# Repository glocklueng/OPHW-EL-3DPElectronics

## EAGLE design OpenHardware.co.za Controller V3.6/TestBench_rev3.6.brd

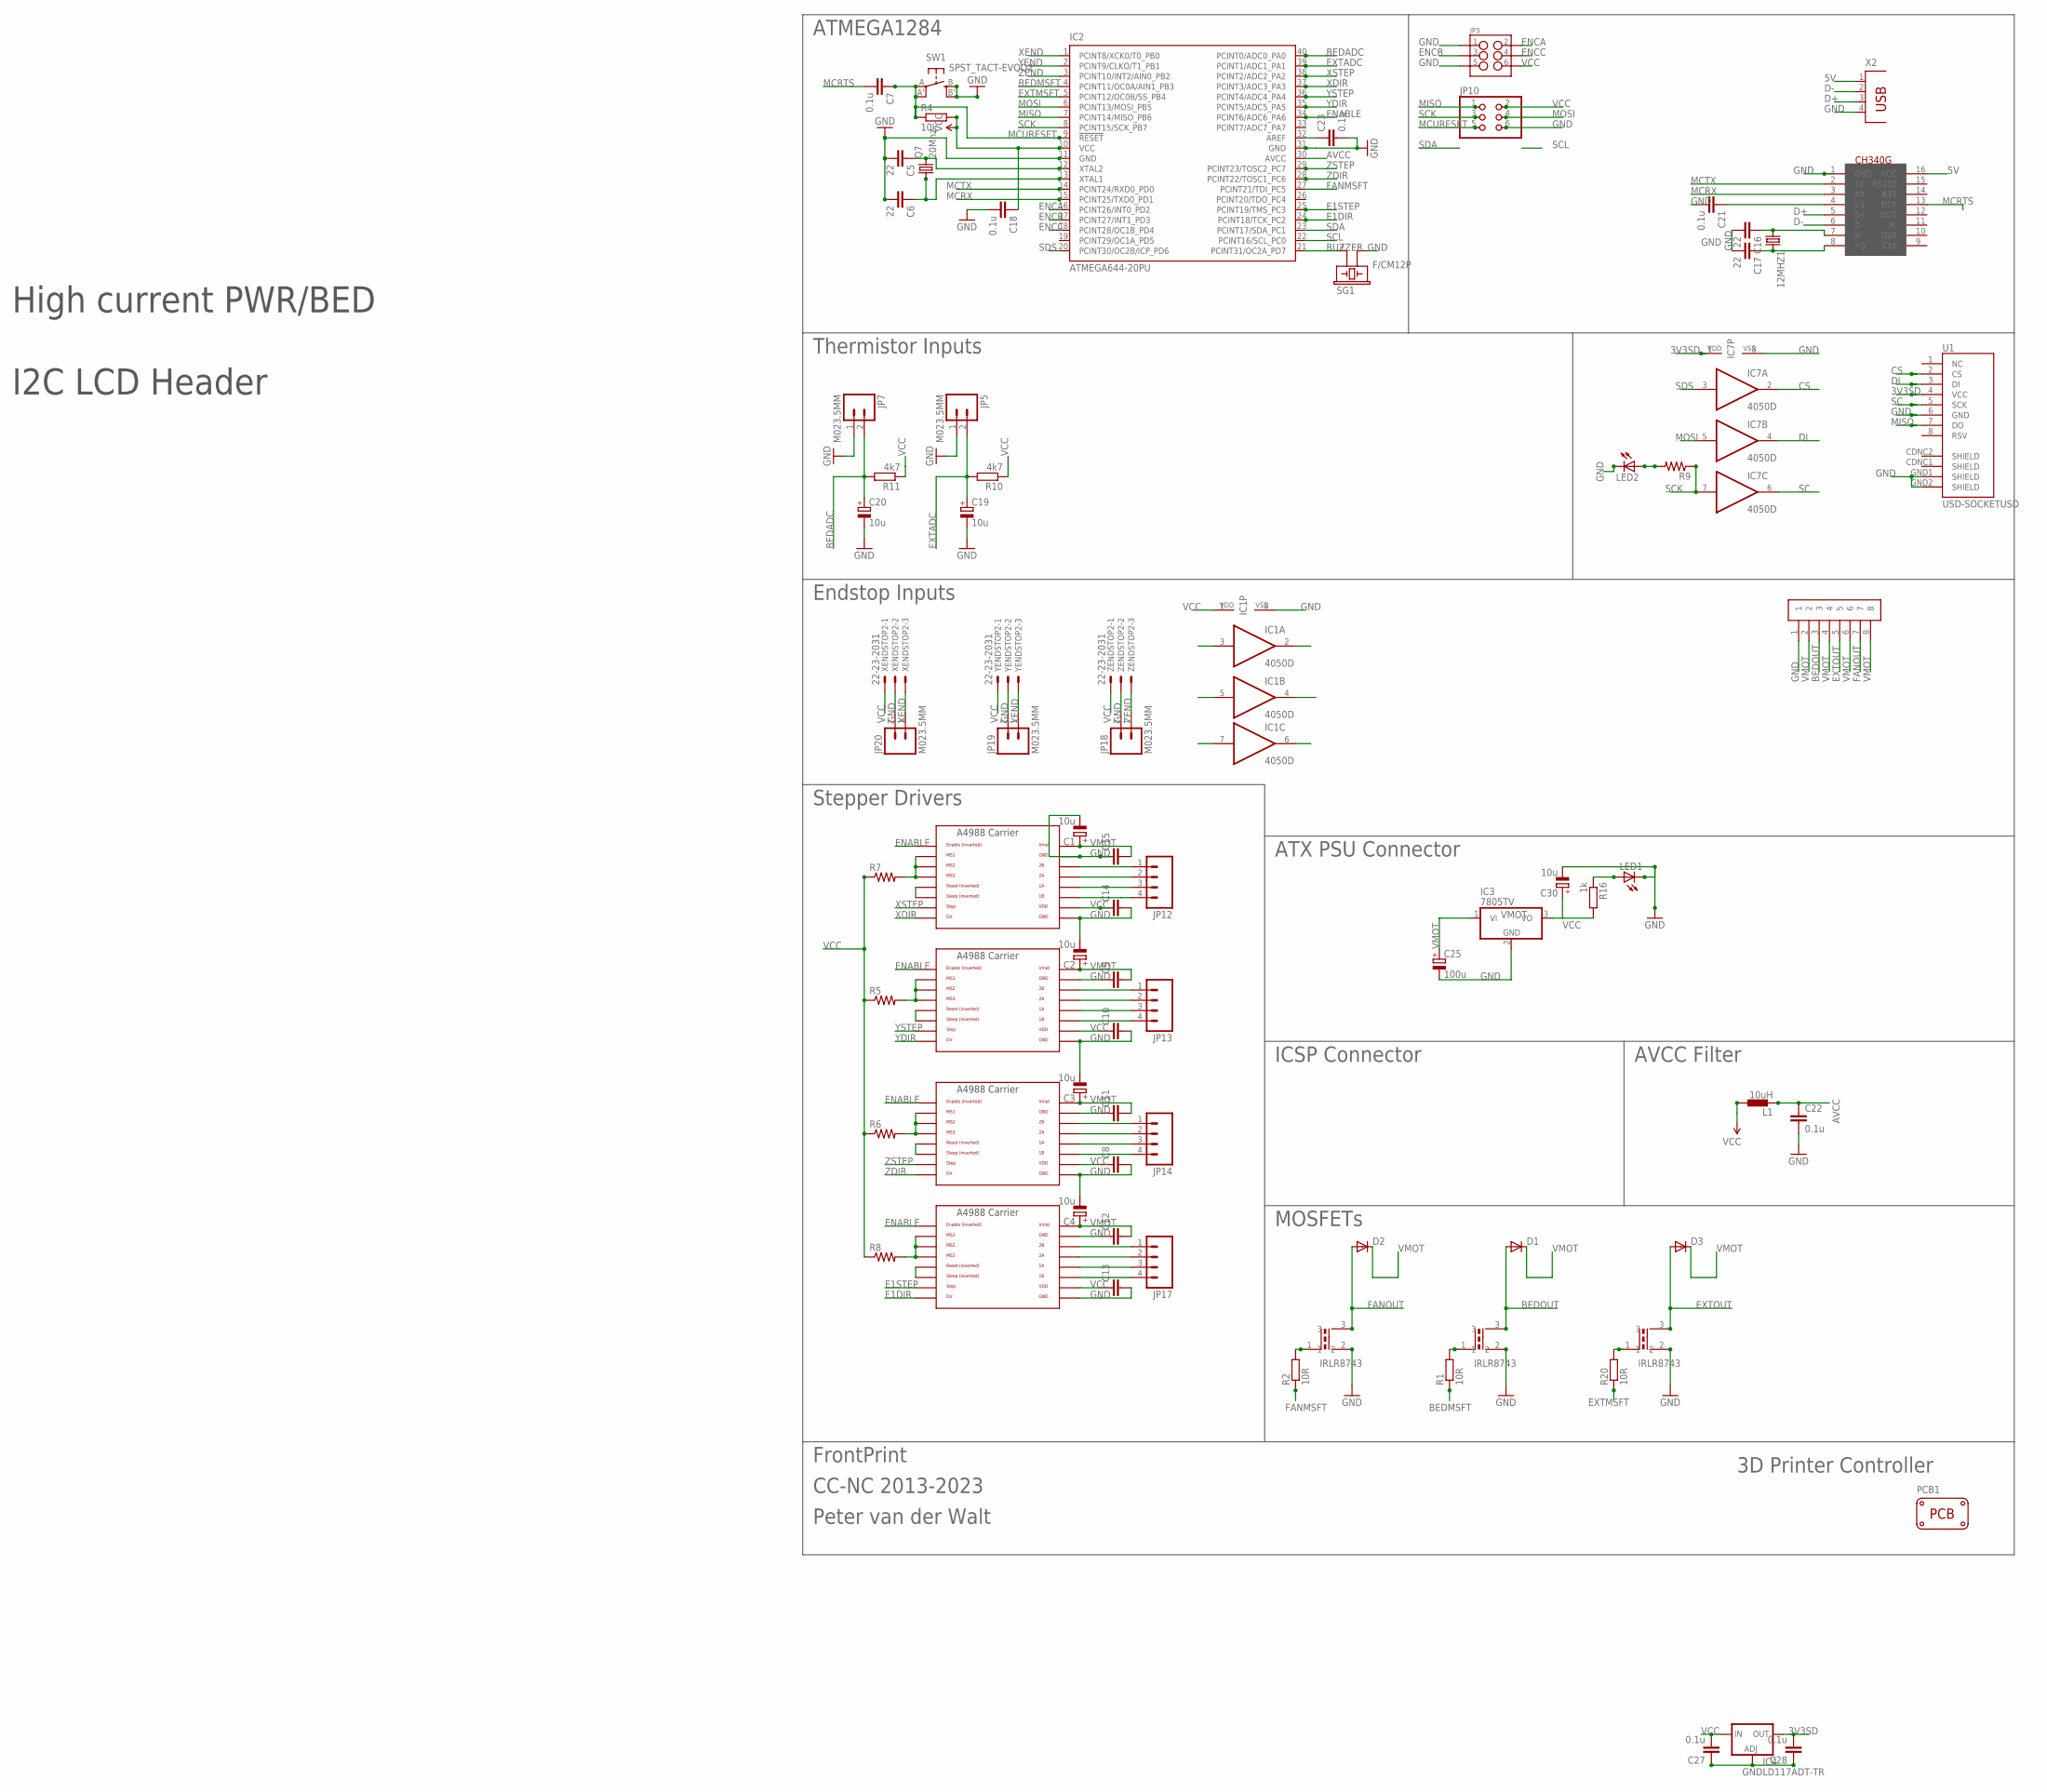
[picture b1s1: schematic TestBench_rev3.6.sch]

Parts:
12MHZ1: CRYSTALHC49UP; HC49UP
C1, C2, C3, C4, C19, C20, C30: 10u; SANYO-OSCON_SMD_B6
C5, C6, C16, C17: 22; 1206
C7, C18, C21, C22, C23, C27, C28: 0.1u; 1206
C8, C9, C10, C11, C12, C13, C14, C15: CAP1206; 1206
C25: 100u; E5-8,5
D1, D2, D3: DIODESMA-ALT; SMA-DIODE_ALT
E1POL: POLOLU_A4983CARRIER; A4988BREAKOUT
IC1, IC7: 4050D; SO16
IC2: ATMEGA644-20PU; DIL40
IC3: 7805TV; TO220V
IC4: LD117ADT-TR; DPACK
JP3: M03X2SHROUD; 2X3-SHROUDED
JP5, JP7, JP18, JP19, JP20: M023.5MM; SCREWTERMINAL-3.5MM-2
JP10: PINHD-2X3/90; 2X03/90
JP12, JP13, JP14, JP17: M04SCREW; SCREWTERMINAL-3.5MM-4
L1: 10uH; BL01RN1A
LED1, LED2: LEDSMT1206; 1206
PCB1: PCB_DP_SQUARE-10X10; DP100100_V1
Q7: 20Mhz; HC49UP
R1, R2, R20: 10R; M1206
R4: 10k; M1206
R5, R6, R7, R8: RESISTOR1206; 1206
R9: R-US_M1206; M1206
R10, R11: 4k7; M1206
R16: 1k; M1206
SG1: F/CM12P
SW1: SPST_TACT-EVQQ2; EVQ-Q2
U1: USD-SOCKETUSD; USD-SOCKET-PP
U$1, U$3, U$4: IRLR8743; TO263
U$2: CH340G; SOIC16
U$5: XY825A-8P
X2: PN61729
XENDSTOP2: 22-23-2031
XPOL: POLOLU_A4983CARRIER; A4988BREAKOUT
YENDSTOP2: 22-23-2031
YPOL: POLOLU_A4983CARRIER; A4988BREAKOUT
ZENDSTOP2: 22-23-2031
ZPOL: POLOLU_A4983CARRIER; A4988BREAKOUT

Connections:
3V3SD: C28.2, IC4.4 (OUT), IC7.1 (VDD), U1.4 (VCC)
5V: U$2.16 (VCC), X2.1
AVCC: C22.1, IC2.30 (AVCC), L1.1
BEDADC: C20.+, IC2.40 (PCINT0/ADC0_PA0), JP7.2, R11.2
BEDMSFT: IC2.4 (PCINT11/OC0A/AIN1_PB3), R1.1
BEDOUT: D1.A, U$3.3, U$5.3
BUZZER: IC2.21 (PCINT31/OC2A_PD7), SG1.+ (1)
CS: IC7.2 (O), U1.2 (CS)
D+: U$2.5 (D+), X2.3
D-: U$2.6 (D-), X2.2
DI: IC7.4 (O), U1.3 (DI)
E1DIR: E1POL.DIR, IC2.24 (PCINT18/TCK_PC2)
E1STEP: E1POL.STEP, IC2.25 (PCINT19/TMS_PC3)
ENABLE: E1POL.EN, IC2.34 (PCINT6/ADC6_PA6), XPOL.EN, YPOL.EN, ZPOL.EN
ENCA: IC2.16 (PCINT26/INT0_PD2), JP3.2
ENCB: IC2.17 (PCINT27/INT1_PD3), JP3.3
ENCC: IC2.18 (PCINT28/OC1B_PD4), JP3.4
EXTADC: C19.+, IC2.39 (PCINT1/ADC1_PA1), JP5.2, R10.2
EXTMSFT: IC2.5 (PCINT12/OC0B/SS_PB4), R20.1
EXTOUT: D3.A, U$1.3, U$5.5
FANMSFT: IC2.27 (PCINT21/TDI_PC5), R2.1
FANOUT: D2.A, U$4.3, U$5.7
GND: C1.-, C2.-, C3.-, C4.-, C5.2, C6.2, C8.2, C9.1, C10.2, C11.1, C12.1, C13.2, C14.2, C15.1, C16.2, C17.2, C18.2, C19.-, C20.-, C21.2, C22.2, C23.2, C25.-, C27.1, C28.1, C30.-, E1POL.GND, E1POL.GND@0 (GND), IC1.8 (VSS), IC2.11 (GND), IC2.31 (GND), IC3.2 (GND), IC4.1 (ADJ), IC7.8 (VSS), JP3.1, JP3.5, JP5.1, JP7.1, JP10.6, JP18.2, JP19.2, JP20.2, LED1.C, LED2.C, SG1.- (2), SW1.B (S), SW1.B' (S1), U1.6 (GND), U1.GND1 (SHIELD), U1.GND2 (SHIELD), U$1.2 (1), U$2.1 (GND), U$3.2 (1), U$4.2 (1), U$5.1, X2.4, XENDSTOP2.2, XPOL.GND, XPOL.GND@0 (GND), YENDSTOP2.2, YPOL.GND, YPOL.GND@0 (GND), ZENDSTOP2.2, ZPOL.GND, ZPOL.GND@0 (GND)
MCRTS: C7.2, U$2.13 (DTR)
MCRX: IC2.15 (PCINT25/TXD0_PD1), U$2.3 (RX)
MCTX: IC2.14 (PCINT24/RXD0_PD0), U$2.2 (TX)
MCURESET: C7.1, IC2.9 (!RESET), JP10.5, R4.1, SW1.A, SW1.A' (P1)
MISO: IC2.7 (PCINT14/MISO_PB6), JP10.1, U1.7 (DO)
MOSI: IC2.6 (PCINT13/MOSI_PB5), IC7.5 (I), JP10.4
unnamed: R1.2, U$3.1 (2)
unnamed: R2.2, U$4.1 (2)
unnamed: C5.1, IC2.12 (XTAL2), Q7.2
unnamed: C6.1, IC2.13 (XTAL1), Q7.1
unnamed: E1POL.RST, E1POL.SLP (SLEEP)
unnamed: ZPOL.RST, ZPOL.SLP (SLEEP)
unnamed: YPOL.RST, YPOL.SLP (SLEEP)
unnamed: XPOL.RST, XPOL.SLP (SLEEP)
unnamed: R7.2, XPOL.MS1, XPOL.MS2, XPOL.MS3
unnamed: R5.2, YPOL.MS1, YPOL.MS2, YPOL.MS3
unnamed: E1POL.MS1, E1POL.MS2, E1POL.MS3, R8.2
unnamed: R6.2, ZPOL.MS1, ZPOL.MS2, ZPOL.MS3
unnamed: E1POL.1B, JP17.4
unnamed: E1POL.1A, JP17.3
unnamed: E1POL.2A, JP17.2
unnamed: E1POL.2B, JP17.1
unnamed: JP14.4, ZPOL.1B
unnamed: JP14.3, ZPOL.1A
unnamed: JP14.2, ZPOL.2A
unnamed: JP14.1, ZPOL.2B
unnamed: JP13.1, YPOL.2B
unnamed: JP13.2, YPOL.2A
unnamed: JP13.3, YPOL.1A
unnamed: JP13.4, YPOL.1B
unnamed: JP12.4, XPOL.1B
unnamed: JP12.3, XPOL.1A
unnamed: JP12.2, XPOL.2A
unnamed: JP12.1, XPOL.2B
unnamed: 12MHZ1.1, C16.1, U$2.7 (XI)
unnamed: LED2.A, R9.2
unnamed: 12MHZ1.2, C17.1, U$2.8 (XO)
unnamed: C21.1, U$2.4 (V3)
unnamed: R20.2, U$1.1 (2)
unnamed: C23.1, IC2.32 (AREF)
unnamed: LED1.A, R16.1
SC: IC7.6 (O), U1.5 (SCK)
SCK: IC2.8 (PCINT15/SCK_PB7), IC7.7 (I), JP10.3, R9.1
SCL: IC2.22 (PCINT16/SCL_PC0)
SDA: IC2.23 (PCINT17/SDA_PC1)
SDS: IC2.20 (PCINT30/OC2B/ICP_PD6), IC7.3 (I)
VCC: C8.1, C10.1, C13.1, C14.1, C18.1, C27.2, C30.+, E1POL.VDD, IC1.1 (VDD), IC2.10 (VCC), IC3.3 (VO), IC4.3 (IN), JP3.6, JP10.2, L1.2, R4.2, R5.1, R6.1, R7.1, R8.1, R10.1, R11.1, R16.2, XENDSTOP2.1, XPOL.VDD, YENDSTOP2.1, YPOL.VDD, ZENDSTOP2.1, ZPOL.VDD
VMOT: C1.+, C2.+, C3.+, C4.+, C9.2, C11.2, C12.2, C15.2, C25.+, D1.C, D2.C, D3.C, E1POL.VMOT, IC3.1 (VI), U$5.2, U$5.4, U$5.6, U$5.8, XPOL.VMOT, YPOL.VMOT, ZPOL.VMOT
XDIR: IC2.37 (PCINT3/ADC3_PA3), XPOL.DIR
XEND: IC2.1 (PCINT8/XCK0/T0_PB0), JP20.1, XENDSTOP2.3
XSTEP: IC2.38 (PCINT2/ADC2_PA2), XPOL.STEP
YDIR: IC2.35 (PCINT5/ADC5_PA5), YPOL.DIR
YEND: IC2.2 (PCINT9/CLKO/T1_PB1), JP19.1, YENDSTOP2.3
YSTEP: IC2.36 (PCINT4/ADC4_PA4), YPOL.STEP
ZDIR: IC2.28 (PCINT22/TOSC1_PC6), ZPOL.DIR
ZEND: IC2.3 (PCINT10/INT2/AIN0_PB2), JP18.1, ZENDSTOP2.3
ZSTEP: IC2.29 (PCINT23/TOSC2_PC7), ZPOL.STEP

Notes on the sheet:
Thermistor Inputs
Endstop Inputs
Stepper Drivers
AVCC Filter
ATX PSU Connector
ICSP Connector
MOSFETs
ATMEGA1284
FrontPrint
CC-NC 2013-2023
Peter van der Walt
3D Printer Controller
High current PWR/BED
I2C LCD Header

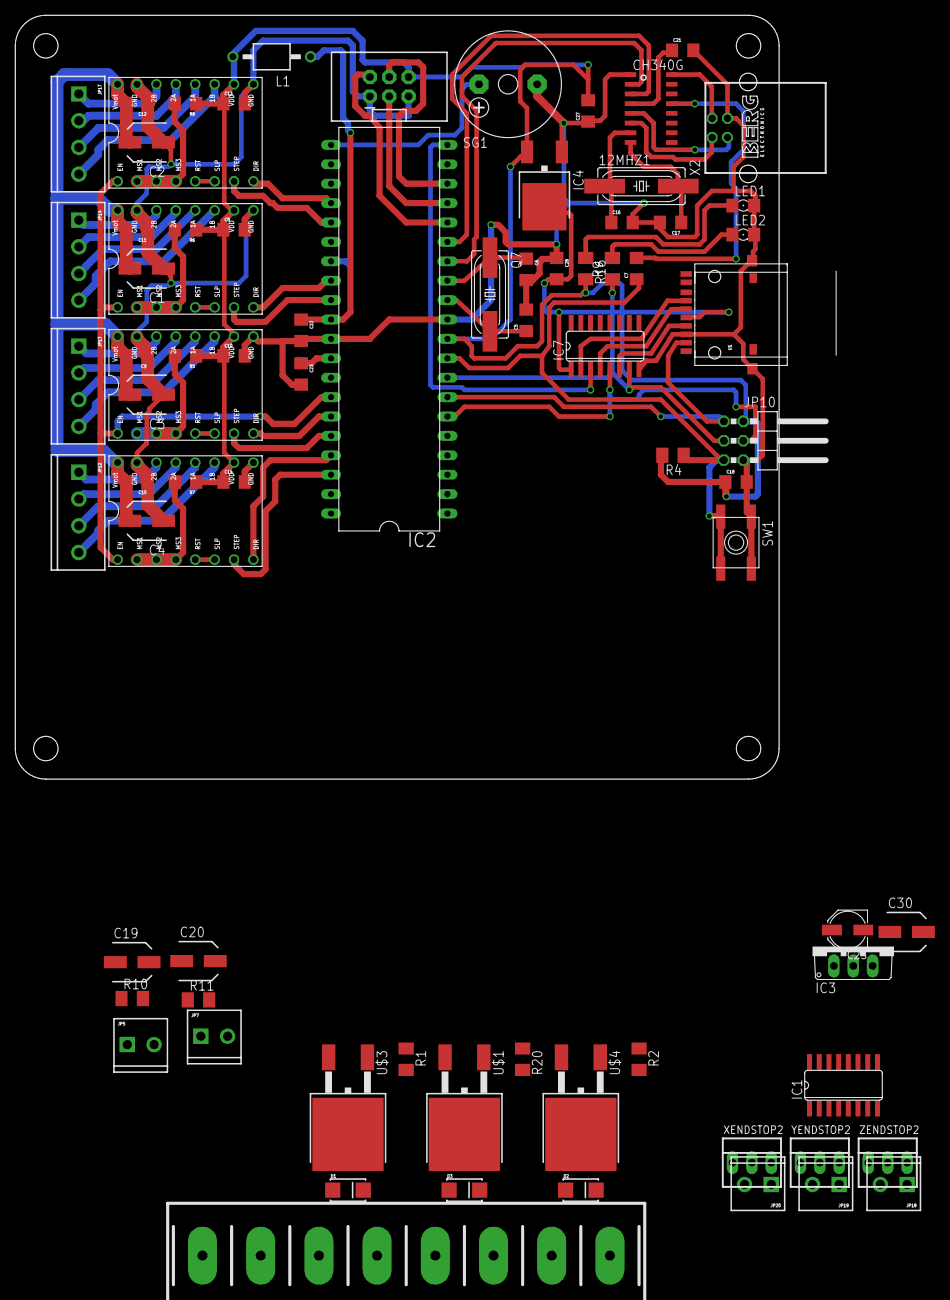
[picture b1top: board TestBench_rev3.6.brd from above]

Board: 2 copper layers, 100.0 x 100.0 mm, 80 parts (0 on the bottom side), 78 nets.

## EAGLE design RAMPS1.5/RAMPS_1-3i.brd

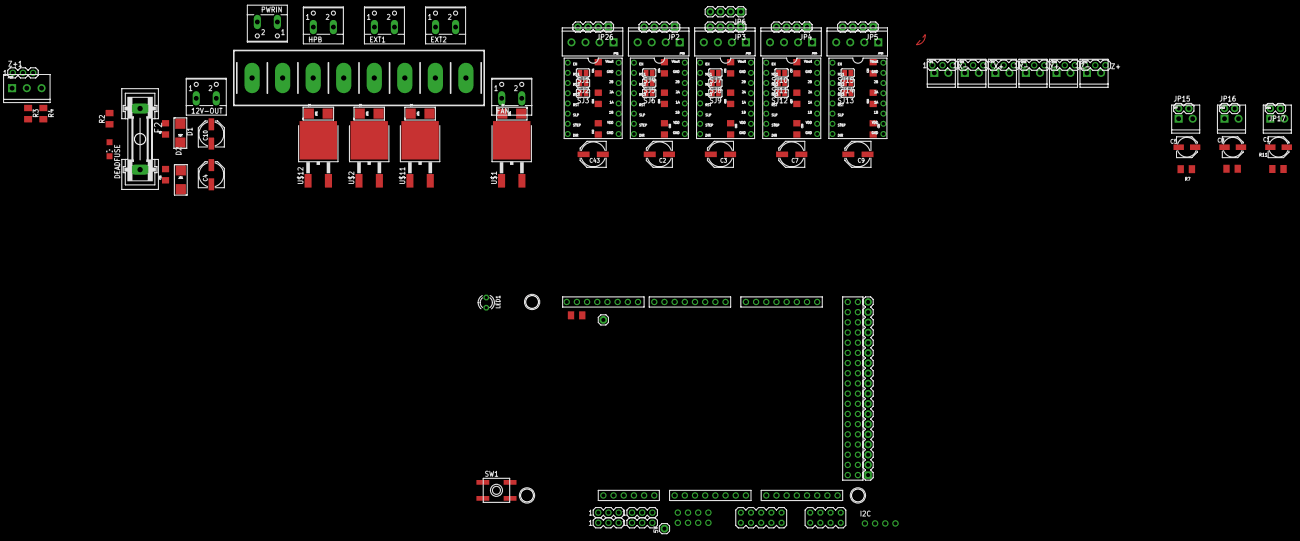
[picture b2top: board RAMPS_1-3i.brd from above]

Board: 2 copper layers, 119 parts (0 on the bottom side), 129 nets, no tracks yet.

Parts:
5V: 1X01
12V-OUT: W237-102
A-OUT: 1X04
C1, C5, C8: 10uF; PANASONIC_C
C2, C3, C7, C9, C43: 100U; PANASONIC_D
C4, C10: 470U; PANASONIC_D
C6, C11: 100n; 1206
C33, C34, C35, C36, C37, C38, C39, C40, C41, C42: 1206
D1, D2, D3, D4, D5, D6: SMADIODE
DEADFUSE: CHIPLED_1206
E1POL1, E2POL1: POLOLU_A4983CARRIER; A4988BREAKOUT
EXT1, EXT2: W237-102
F2: FUSEGSH15; GSH15
FAN: W237-102
HPB: W237-102
I2C: 1X04
JP1, JP7, JP8, JP9, JP10, JP11, JP12, JP13, JP14: M023.5MM; SCREWTERMINAL-3.5MM-2
JP2, JP3, JP4, JP5, JP6, JP26: 1X04
JP15, JP16, JP17: M02PTH; 1X02
JP18: SCREWTERMINAL-3.5MM-3_LOCK.007S
JP21, JP22, JP23, JP24, JP25: SCREWTERMINAL-3.5MM-4
LED1: LED3MM
PS-ON: 1X01
PWRIN: W237-102
R1, R7, R11: 4.7K; M1206
R2, R12: 1K; M1206
R3: 15K; M1206
R4: 10K; M1206
R24, R25, R26, R27, R28: 1206
SER1, SER2, SER3, SER4: 3PIN-HEADER
SERIAL: 1X04
SJ1, SJ2, SJ3, SJ4, SJ5, SJ6, SJ7, SJ8, SJ9, SJ10, SJ11, SJ12, SJ13, SJ14, SJ15: SJ
SW1: SPST_TACT-EVQQ2; EVQ-Q2
U1: ARDUINO_MEGA_SHIELD
U$1, U$2, U$11, U$12: IRLR8743; TO263
U$3: M04X2; 2X4
U$4: XY825A-8P
U$9: M18_; 1X18
U$10: M05X2; 2X5
X+: 3PIN-HEADER
X-: 3PIN-HEADER
XPOL1: POLOLU_A4983CARRIER; A4988BREAKOUT
Y+: 3PIN-HEADER
Y-: 3PIN-HEADER
YPOL1: POLOLU_A4983CARRIER; A4988BREAKOUT
Z+, Z+1: 3PIN-HEADER
Z-: 3PIN-HEADER
ZPOL1: POLOLU_A4983CARRIER; A4988BREAKOUT

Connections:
12V: JP18.1, Z+1.1
+12V: 12V-OUT.1, C6.2, C10.+, D1.A, D6.C, FAN.2
+24V: C4.+, C11.2, D2.C, D3.C, D4.C, D5.C, DEADFUSE.C, EXT1.2, EXT2.2, F2.2, HPB.2, U$4.6, U$4.8
A3: SERIAL.3, U1.A3
A4: SERIAL.4, U1.A4
A5: U1.A5, U$10.3
A9: U1.A9, U$10.4
A10: U1.A10, U$10.5
A11: U1.A11, U$10.10
A12: U1.A12, U$10.9
AM-VIN: D1.C, U1.VIN
BEDOUT: D3.A, HPB.1, U$2.3, U$4.3
D1: A-OUT.4, U1.RX
D2: A-OUT.3, U1.TX
D4: SER4.3, U1.D4
D5: SER3.3, U1.D5
D6: SER2.3, U1.D6
D7: SER1.3, U1.D7
D8-HPB: U1.D8, U$2.1
D9-E2: U1.D9, U$11.1
D10-E1: U1.D10, U$12.1
D12: PS-ON.1, U1.D12
D16: U1.D16, U$9.18
D17: U1.D17, U$9.17
D23: U1.D23, U$9.16
D25: U1.D25, U$9.15
D27: U1.D27, U$9.14
D29: U1.D29, U$9.13
D31: U1.D31, U$9.12
D32: U1.D32, U$9.3
D33: U1.D33, U$9.11
D35: U1.D35, U$9.10
D37: U1.D37, U$9.9
D39: U1.D39, U$9.8
D40: U1.D40, U$10.6
D41: U1.D41, U$9.7
D42: U1.D42, U$10.8
D43: U1.D43, U$9.6
D44: U1.D44, U$10.7
D45: U1.D45, U$9.5
D47: U1.D47, U$9.4
D49: U1.D49, U$3.2
D53: U1.D53, U$3.6
E0-DIR: E1POL1.DIR, U1.D28
E0-EN: E1POL1.EN, U1.D24
E0-STEP: E1POL1.STEP, U1.D26
E1-DIR: E2POL1.DIR, U1.D34
E1-EN: E2POL1.EN, U1.D30
E1-STEP: E2POL1.STEP, U1.D36
E1OUT: D4.A, EXT1.1, U$4.5, U$12.3
E2OUT: D5.A, EXT2.1, U$4.7, U$11.3
FANOUT: D6.A, FAN.1, U$1.3
GND: 12V-OUT.2, A-OUT.2, C1.-, C2.-, C3.-, C4.-, C5.-, C6.1, C7.-, C8.-, C9.-, C10.-, C11.1, C33.2, C34.1, C35.2, C36.1, C37.1, C38.2, C39.2, C40.1, C41.1, C42.2, C43.-, D2.A, E1POL1.GND, E1POL1.GND@0, E2POL1.GND, E2POL1.GND@0, I2C.2, JP1.2, JP7.1, JP8.2, JP9.2, JP10.2, JP11.2, JP12.2, JP13.1, JP14.1, JP15.1, JP16.1, JP17.1, JP18.3, LED1.K, PWRIN.2, R4.1, SER1.1, SER2.1, SER3.1, SER4.1, SERIAL.2, SW1.A, SW1.A', U1.GND@0, U1.GND@1, U1.GND@3, U1.GND@4, U$1.2, U$2.2, U$3.7, U$4.1, U$9.2, U$10.2, U$11.2, U$12.2, X+.2, X-.2, XPOL1.GND, XPOL1.GND@0, Y+.2, Y-.2, YPOL1.GND, YPOL1.GND@0, Z+.2, Z+1.3, Z-.2, ZPOL1.GND, ZPOL1.GND@0
LED: R12.2, U1.D13
MISO: U1.D50, U$3.3
MOSI: U1.D51, U$3.4
unnamed: DEADFUSE.A, R2.1
unnamed: SJ2.2, XPOL1.MS2
unnamed: SJ1.2, XPOL1.MS1
unnamed: SJ4.2, YPOL1.MS1
unnamed: SJ5.2, YPOL1.MS2
unnamed: SJ7.2, ZPOL1.MS1
unnamed: SJ8.2, ZPOL1.MS2
unnamed: SJ9.2, ZPOL1.MS3
unnamed: SJ6.2, YPOL1.MS3
unnamed: SJ3.2, XPOL1.MS3
unnamed: E2POL1.MS2, SJ14.2
unnamed: E2POL1.MS3, SJ13.2
unnamed: E2POL1.MS1, SJ15.2
unnamed: E1POL1.MS3, SJ12.2
unnamed: E1POL1.MS1, SJ10.2
unnamed: E1POL1.MS2, SJ11.2
unnamed: LED1.A, R12.1
unnamed: E1POL1.RST, E1POL1.SLP
unnamed: ZPOL1.RST, ZPOL1.SLP
unnamed: YPOL1.RST, YPOL1.SLP
unnamed: XPOL1.RST, XPOL1.SLP
unnamed: R26.2, SJ1.1, SJ2.1, SJ3.1
unnamed: R24.2, SJ4.1, SJ5.1, SJ6.1
unnamed: R27.2, SJ10.1, SJ11.1, SJ12.1
unnamed: R25.2, SJ7.1, SJ8.1, SJ9.1
unnamed: E1POL1.1B, JP4.4, JP24.4
unnamed: E1POL1.1A, JP4.3, JP24.3
unnamed: E1POL1.2A, JP4.2, JP24.2
unnamed: E1POL1.2B, JP4.1, JP24.1
unnamed: JP3.4, JP6.4, JP23.4, ZPOL1.1B
unnamed: JP3.3, JP6.3, JP23.3, ZPOL1.1A
unnamed: JP3.2, JP6.2, JP23.2, ZPOL1.2A
unnamed: JP3.1, JP6.1, JP23.1, ZPOL1.2B
unnamed: JP2.1, JP22.1, YPOL1.2B
unnamed: JP2.2, JP22.2, YPOL1.2A
unnamed: JP2.3, JP22.3, YPOL1.1A
unnamed: JP2.4, JP22.4, YPOL1.1B
unnamed: JP21.4, JP26.4, XPOL1.1B
unnamed: JP21.3, JP26.3, XPOL1.1A
unnamed: JP21.2, JP26.2, XPOL1.2A
unnamed: JP21.1, JP26.1, XPOL1.2B
unnamed: E2POL1.RST, E2POL1.SLP
unnamed: R28.2, SJ13.1, SJ14.1, SJ15.1
unnamed: E2POL1.1B, JP5.4, JP25.4
unnamed: E2POL1.1A, JP5.3, JP25.3
unnamed: E2POL1.2A, JP5.2, JP25.2
unnamed: E2POL1.2B, JP5.1, JP25.1
PWRIN: F2.1, PWRIN.1, R2.2, U$4.2
RESET: SW1.B, SW1.B', U1.RES
SCK: U1.D52, U$3.5
SCL: I2C.4, U1.D21
SDA: I2C.3, U1.D20
SENSOROUT: JP18.2, R3.1, Z+1.2
THERM0: C5.+, JP7.2, JP15.2, R7.1, U1.A13
THERM1: C8.+, JP13.2, JP16.2, R1.1, U1.A14
THERM2: C1.+, JP14.2, JP17.2, R11.1, U1.A15
VCC: 5V.1, A-OUT.1, C33.1, C35.1, C38.1, C39.1, C42.1, E1POL1.VDD, E2POL1.VDD, I2C.1, R1.2, R7.2, R11.2, R24.1, R25.1, R26.1, R27.1, R28.1, SER1.2, SER2.2, SER3.2, SER4.2, SERIAL.1, U1.5V@0, U1.5V@1, U1.5V@2, U$3.1, U$9.1, U$10.1, X+.3, X-.3, XPOL1.VDD, Y+.3, Y-.3, YPOL1.VDD, Z+.3, Z-.3, ZPOL1.VDD
VMOT: C2.+, C3.+, C7.+, C9.+, C34.2, C36.2, C37.2, C40.2, C41.2, C43.+, E1POL1.VMOT, E2POL1.VMOT, XPOL1.VMOT, YPOL1.VMOT, ZPOL1.VMOT
X-DIR: U1.A1, XPOL1.DIR
X-EN: U1.D38, XPOL1.EN
X-MAX: JP8.1, U1.D2, X+.1
X-MIN: JP1.1, U1.D3, X-.1
X-STEP: U1.A0, XPOL1.STEP
Y-DIR: U1.A7, YPOL1.DIR
Y-EN: U1.A2, YPOL1.EN
Y-MAX: JP10.1, U1.D15, Y+.1
Y-MIN: JP9.1, U1.D14, Y-.1
Y-STEP: U1.A6, YPOL1.STEP
Z-DIR: U1.D48, ZPOL1.DIR
Z-EN: U1.A8, ZPOL1.EN
Z-MAX: JP12.1, U1.D19, Z+.1
Z-MIN: JP11.1, R3.2, R4.2, U1.D18, Z-.1
Z-STEP: U1.D46, ZPOL1.STEP

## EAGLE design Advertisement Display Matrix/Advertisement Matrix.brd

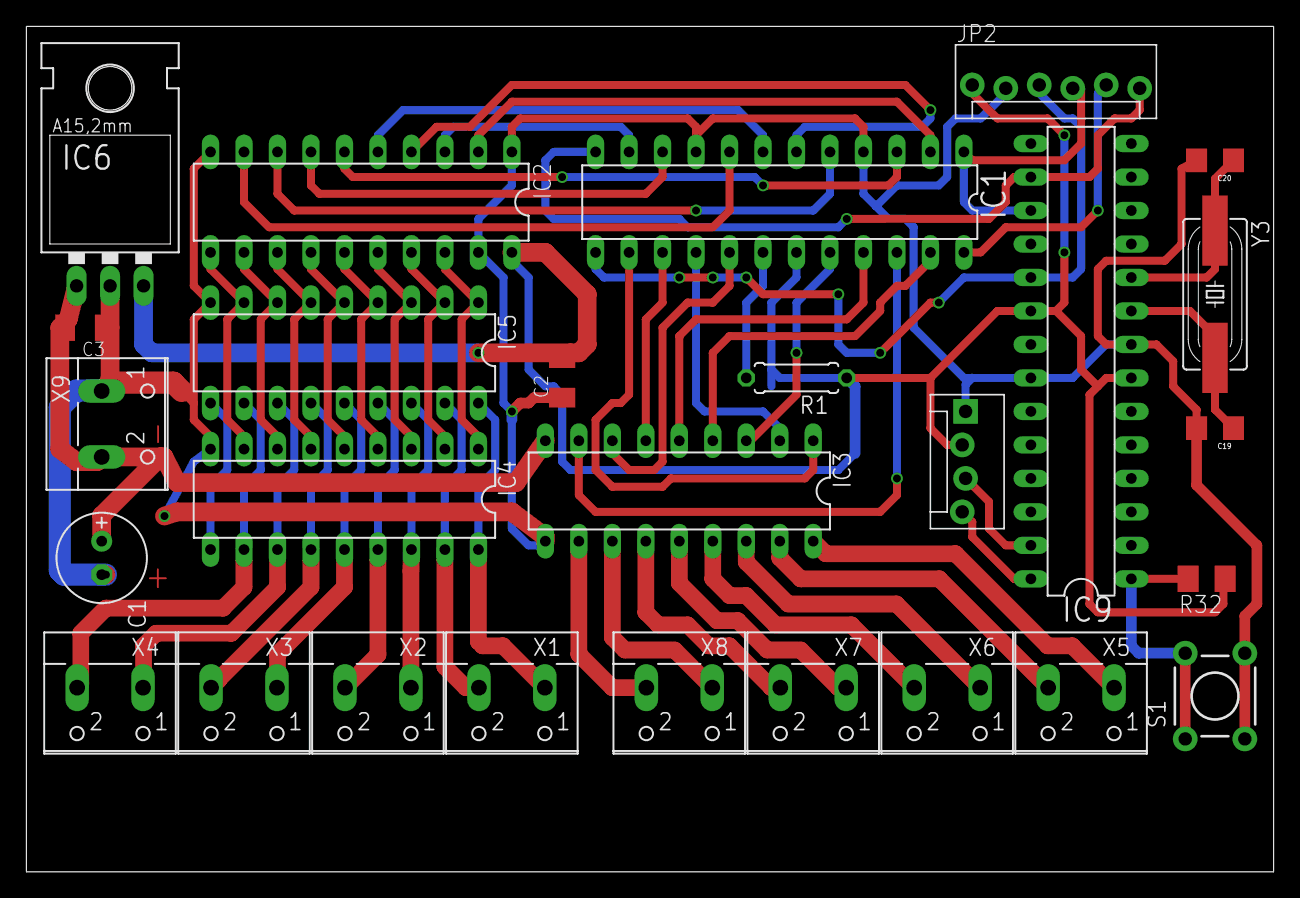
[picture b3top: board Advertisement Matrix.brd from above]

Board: 2 copper layers, 94.6 x 64.1 mm, 27 parts (0 on the bottom side), 54 nets.

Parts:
C1: E2,5-7
C2, C3: C1206K
C19, C20: 22p; 1206
IC1: MAX7219CNG; DIL24-3
IC2: 74HC540N; DIL20
IC3: UDN2981A; DIL18
IC4, IC5: DIL18
IC6: 78XXL
IC9: ATMEGA168-20P; DIL28-3
JP1: MOLEX-1X4_LOCK
JP2: MOLEX-1X6_LOCK
R1: 0207/7
R32: 10k; M1206
S1: TACTILE-PTH
X1, X2, X3, X4, X5, X6, X7, X8, X9: W237-102
Y3: 16Mhz; HC49UP

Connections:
12V: C1.+, C3.2, IC3.9, IC6.IN, X9.2
CS: IC1.12, IC9.16, JP2.6
DO: IC1.24, JP2.5
GND: C1.-, C2.1, C3.1, C19.2, C20.2, IC1.4, IC1.9, IC2.1, IC2.10, IC2.19, IC3.10, IC4.9, IC5.9, IC6.GND, IC9.8, IC9.22, JP1.1, JP2.2, S1.3, S1.4, X9.1
LCDRESET: IC9.1, R32.2, S1.1, S1.2
MOSI: IC1.1, IC9.17, JP2.4
unnamed: IC1.2, IC2.2
unnamed: IC1.11, IC2.3
unnamed: IC1.6, IC2.4
unnamed: IC1.7, IC2.5
unnamed: IC1.3, IC2.6
unnamed: IC1.10, IC2.7
unnamed: IC1.5, IC2.8
unnamed: IC1.8, IC2.9
unnamed: IC1.14, IC3.1
unnamed: IC1.16, IC3.2
unnamed: IC1.20, IC3.3
unnamed: IC1.23, IC3.4
unnamed: IC1.21, IC3.5
unnamed: IC1.15, IC3.6
unnamed: IC1.17, IC3.7
unnamed: IC1.22, IC3.8
unnamed: IC2.18, IC4.1, IC5.1
unnamed: IC2.17, IC4.2, IC5.2
unnamed: IC2.16, IC4.3, IC5.3
unnamed: IC2.15, IC4.4, IC5.4
unnamed: IC2.14, IC4.5, IC5.5
unnamed: IC2.13, IC4.6, IC5.6
unnamed: IC2.12, IC4.7, IC5.7
unnamed: IC2.11, IC4.8, IC5.8
unnamed: IC3.18, X5.1
unnamed: IC3.17, X5.2
unnamed: IC3.16, X6.1
unnamed: IC3.15, X6.2
unnamed: IC3.14, X7.1
unnamed: IC3.13, X7.2
unnamed: IC3.12, X8.1
unnamed: IC3.11, X8.2
unnamed: IC4.10, IC5.10
unnamed: IC4.11, IC5.11, X4.2
unnamed: IC4.12, IC5.12, X4.1
unnamed: IC4.13, IC5.13, X3.2
unnamed: IC4.14, IC5.14, X3.1
unnamed: IC4.15, IC5.15, X2.2
unnamed: IC4.16, IC5.16, X2.1
unnamed: IC4.17, IC5.17, X1.2
unnamed: IC4.18, IC5.18, X1.1
unnamed: IC1.18, R1.2
SCK: IC1.13, IC9.19, JP2.3
SCL: IC9.28, JP1.4
SDA: IC9.27, JP1.3
VCC: C2.2, IC1.19, IC2.20, IC6.OUT, IC9.7, IC9.20, JP1.2, JP2.1, R1.1, R32.1
XTAL5: C20.1, IC9.10, Y3.1
XTAL6: C19.1, IC9.9, Y3.2

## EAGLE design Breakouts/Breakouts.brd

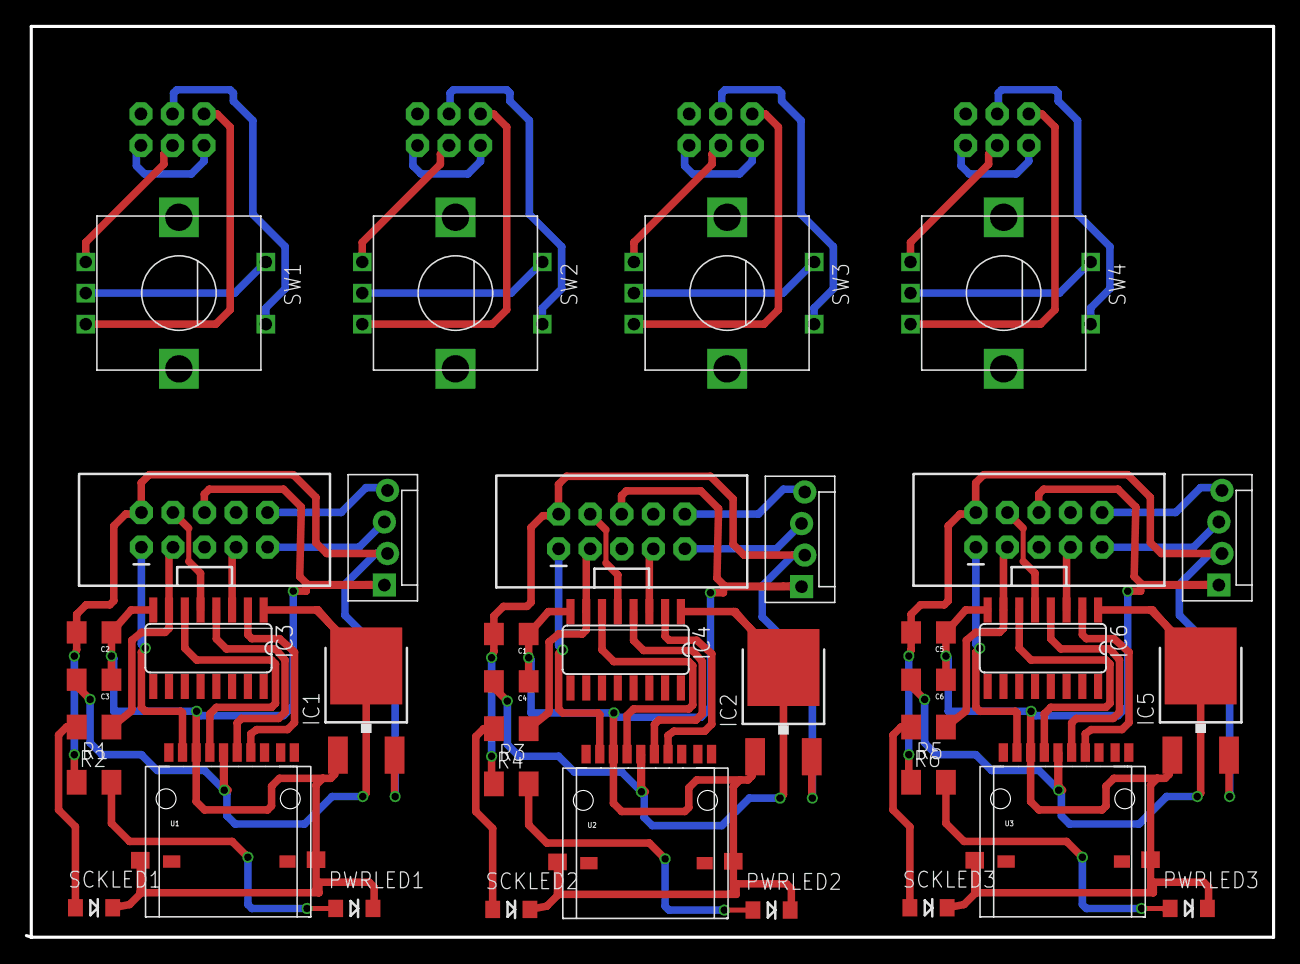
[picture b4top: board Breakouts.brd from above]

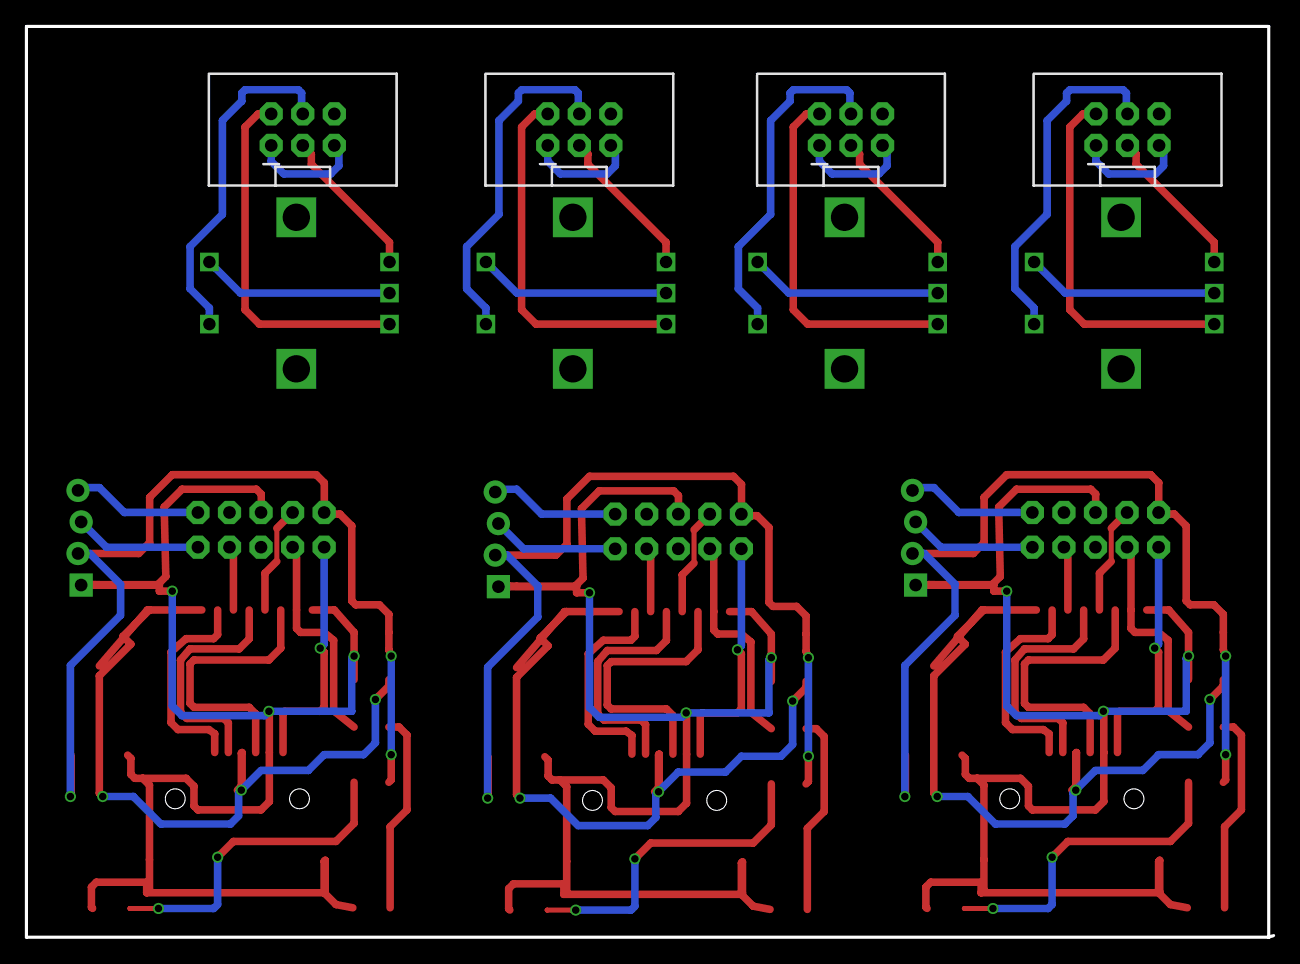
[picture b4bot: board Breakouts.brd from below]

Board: 2 copper layers, 100.0 x 73.3 mm, 41 parts (4 on the bottom side), 61 nets.

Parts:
C1, C2, C3, C4, C5, C6: 0.1u; 1206
IC1, IC2, IC5: LD117ADT-TR; DPACK
IC3, IC4, IC6: 4050D; SO16
JP1, JP4, JP6: M05X2SHD_LOCK; 2X5-SHROUDED_LOCK
JP2, JP8, JP9, JP10: 2X3-SHROUDED
JP3, JP5, JP7: MOLEX-1X4_LOCK
PWRLED1, PWRLED2, PWRLED3: LED-1206
R1, R2, R3, R4, R5, R6: M1206
SCKLED1, SCKLED2, SCKLED3: LED-1206
SW1, SW2, SW3, SW4: EC12E_SW; ALPS_EC12E_SW
U1, U2, U3: USD-SOCKETUSD; USD-SOCKET-PP

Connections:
3V3SD: C3.2, IC1.4, IC3.1, U1.4
3V3SD1: C4.2, IC2.4, IC4.1, U2.4
3V3SD2: C6.2, IC5.4, IC6.1, U3.4
CS: IC3.2, U1.2
CS1: IC4.2, U2.2
CS2: IC6.2, U3.2
DI: IC3.4, U1.3
DI1: IC4.4, U2.3
DI2: IC6.4, U3.3
ENCA: JP2.2, SW1.B
ENCA1: JP8.2, SW2.B
ENCA2: JP9.2, SW3.B
ENCA3: JP10.2, SW4.B
ENCB: JP2.3, SW1.A
ENCB1: JP8.3, SW2.A
ENCB2: JP9.3, SW3.A
ENCB3: JP10.3, SW4.A
ENCC: JP2.4, SW1.E
ENCC1: JP8.4, SW2.E
ENCC2: JP9.4, SW3.E
ENCC3: JP10.4, SW4.E
GND: C2.1, C3.1, IC1.1, IC3.8, JP1.6, JP2.1, JP2.5, JP3.1, PWRLED1.C, SCKLED1.C, U1.6, U1.GND1, U1.GND2
GND1: C1.1, C4.1, IC2.1, IC4.8, JP4.6, JP5.1, PWRLED2.C, SCKLED2.C, U2.6, U2.GND1, U2.GND2
GND2: C5.1, C6.1, IC5.1, IC6.8, JP6.6, JP7.1, PWRLED3.C, SCKLED3.C, U3.6, U3.GND1, U3.GND2
GND3: JP8.1, JP8.5
GND4: JP9.1, JP9.5
GND5: JP10.1, JP10.5
MISO: JP1.1, U1.7
MISO1: JP4.1, U2.7
MISO2: JP6.1, U3.7
MOSI: IC3.5, JP1.4
MOSI1: IC4.5, JP4.4
MOSI2: IC6.5, JP6.4
unnamed: SW1.C, SW1.D
unnamed: R1.2, SCKLED1.A
unnamed: PWRLED1.A, R2.2
unnamed: R3.2, SCKLED2.A
unnamed: PWRLED2.A, R4.2
unnamed: R5.2, SCKLED3.A
unnamed: PWRLED3.A, R6.2
unnamed: SW2.C, SW2.D
unnamed: SW3.C, SW3.D
unnamed: SW4.C, SW4.D
SC: IC3.6, U1.5
SC1: IC4.6, U2.5
SC2: IC6.6, U3.5
SCK: IC3.7, JP1.3, R1.1
SCK1: IC4.7, JP4.3, R3.1
SCK2: IC6.7, JP6.3, R5.1
SCL: JP1.10, JP3.4
SCL1: JP4.10, JP5.4
SCL2: JP6.10, JP7.4
SDA: JP1.9, JP3.3
SDA1: JP4.9, JP5.3
SDA2: JP6.9, JP7.3
SDS: IC3.3, JP1.7
SDS1: IC4.3, JP4.7
SDS2: IC6.3, JP6.7
VCC: C2.2, IC1.3, JP1.2, JP2.6, JP3.2, R2.1
VCC1: C1.2, IC2.3, JP4.2, JP5.2, R4.1
VCC2: C5.2, IC5.3, JP6.2, JP7.2, R6.1

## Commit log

2014-05-25 First Upload to new account
2014-06-09 Added tb6560
2014-08-31 Breakouts for Babybot to ease wiring and v3.5.1 for babyBots
2014-10-05 Misc updates
2014-10-05 Start work on RAMPS 1.5
2014-10-06 IRLR8743 mosfets, 3.5mm endstop terminals, 10mm Barrier Terminals for power
    IRLR8743 mosfets, 3.5mm endstop terminals, 10mm Barrier Terminals for
    power
2014-10-11 Tiny-TinyG, Plus gerbers of Reflow and Advertisement
    Started new project: TinyTinyG
    Generated Gerbers for Advertisement Display driver and ReflowOvenShield
2014-10-12 Added Todo
2014-10-25 Halfway through RAMPS 1.5 wishlist
    Halfway through RAMPS 1.5 wishlist
2014-12-13 HY28 and Ramps1.5
2014-12-16 V3.6 with GooglePlus Interconnect Ideas

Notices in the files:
Advertisement Display Matrix/Advertisement Matrix.brd:
CC-BY-SA
parts and their libraries:
SparkFun-Passives: Licensing: CC v3.0 Share-Alike You are welcome to use this library for commercial purposes.
SparkFun-Connectors: Licensing: Creative Commons ShareAlike 4.0 International - https://creativecommons.org/licenses/by-sa/4.0
